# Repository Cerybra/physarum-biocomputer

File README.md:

<div align="center">
	<h1>Physarum Biocomputer</h1>
</div>

<hr/>

<hr/>

## Project Structure

#### Descriptions

The project structure is organized as follows:

- 📂 `adaptors`: contains all of the hardware files for the various adaptors that are compatible with the biocomputer carrier board.

- 📂 `data`: contains all of the experimentally collected data.

- 📂 `devices`: contains all of the hardware files for both the open-air and enclosure-type devices.

- 📂 `modules`: contains all of the hardware files for each of the biocomputer modules.

- 📂 `software`: contains all of the software used in performing experiments.

- 📂 `simulations`: contains all of the code used in performing equivalent circuit simulations.

- 📂 `plots`: contains all of the code used in producing the main figures.

#### Structure
📂 `repository` 

- 📂 `data`
	- 📂 `device-pulse-recordings` 
	- 📂 `device-regression-recordings` 
	- 📂 `device-sweep-recordings` 
	- 📂 `eis-recordings`
	- 📂 `noise-recordings`
	- 📂 `reservoir-computing-recordings`
- 📂 `modules`
    - 📂 `biocomputer-eval-motherboard`
    - 📂 `dac-eval-module`
    - 📂 `daq-eval-board`
    - 📂 `dual-rail-power-eval-module`
    - 📂 `selector-eval-module`
- 📂 `adaptors`
    - 📂 `1x1-adaptor`
    - 📂 `4x1-adaptor`
	- 📂 `8x1-adaptor`
    - 📂 `card-half`
    - 📂 `card-full`
    - 📂 `configurable-adaptor`
    - 📂 `standard-adaptor`
- 📂 `software`
    - 📂 `examples`
- 📂 `devices`
    - 📂 `enclosures`
    - 📂 `pluggable`
- 📂 `simulations`
- 📂 `plots`

## Reproducibility

To reproduce all of the main figures, either clone the repository or download the `data` directory. Then, run each of the scripts within the `plots/main` directory.

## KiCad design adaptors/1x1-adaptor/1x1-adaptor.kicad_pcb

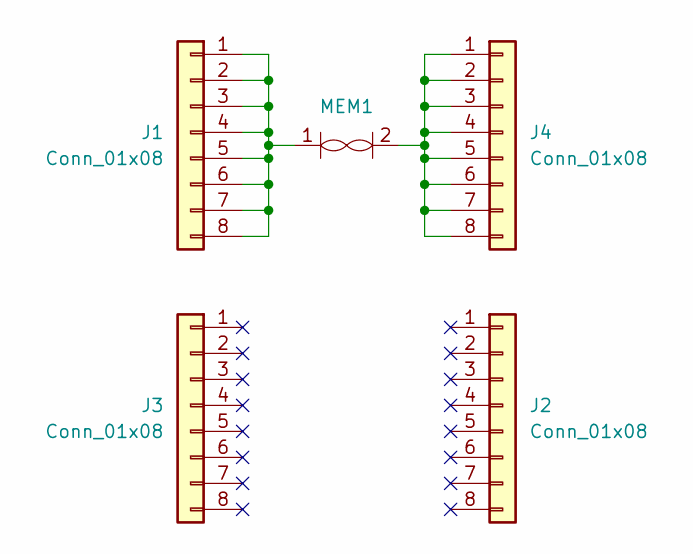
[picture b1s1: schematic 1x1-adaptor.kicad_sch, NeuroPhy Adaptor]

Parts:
J1, J2, J3, J4: Conn_01x08; PinHeader_1x08_P2.54mm_Vertical
MEM1: NeuroPhy_Memristor_5x5mm

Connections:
unnamed: J1.1, J1.2, J1.3, J1.4, J1.5, J1.6, J1.7, J1.8, MEM1.1
unnamed: J4.1, J4.2, J4.3, J4.4, J4.5, J4.6, J4.7, J4.8, MEM1.2

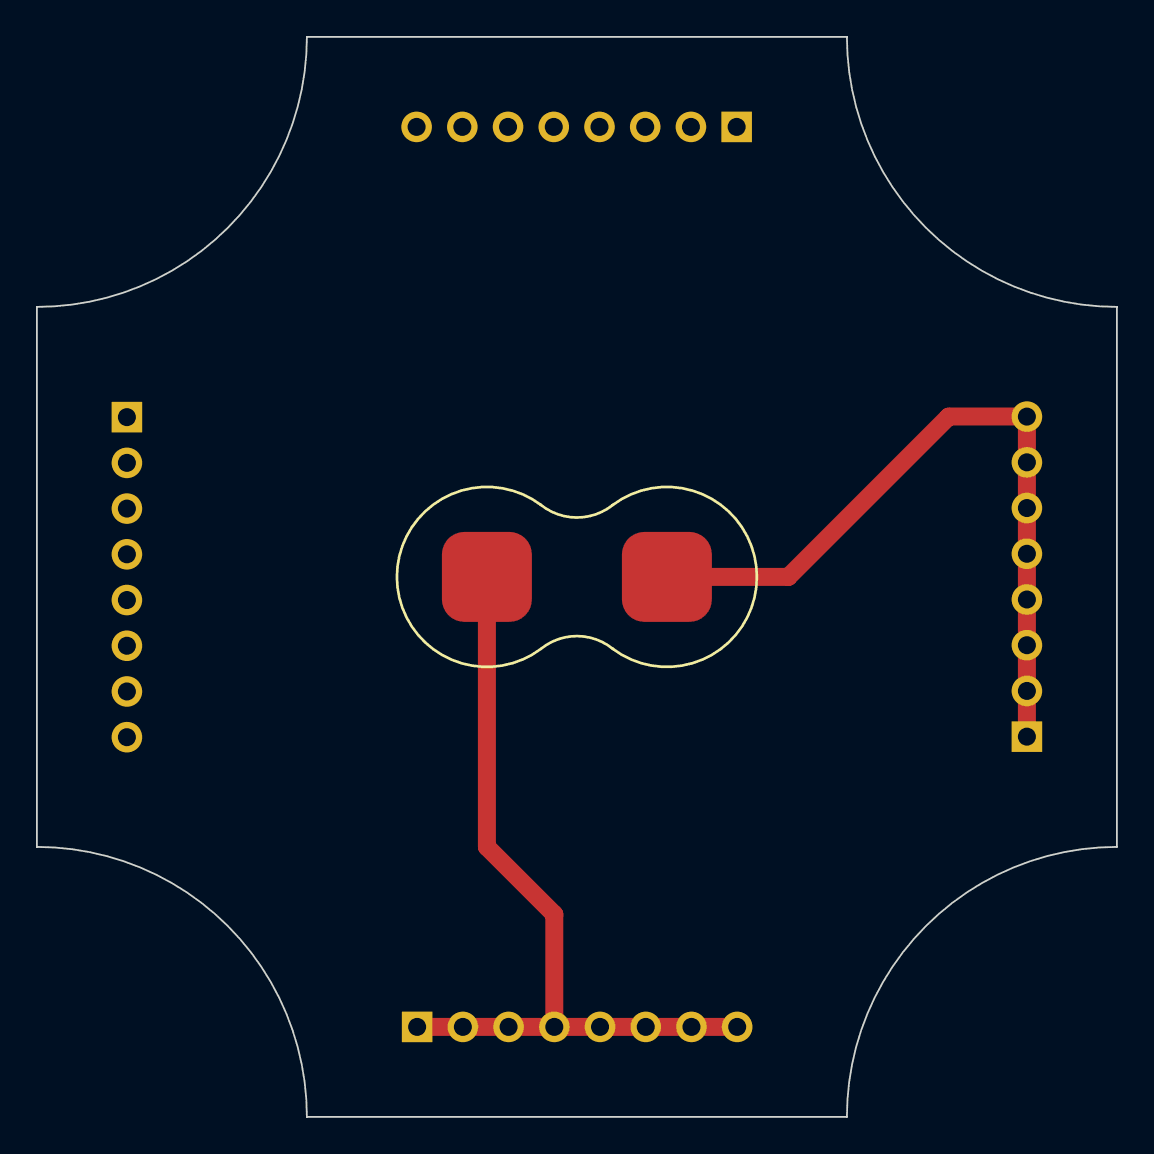
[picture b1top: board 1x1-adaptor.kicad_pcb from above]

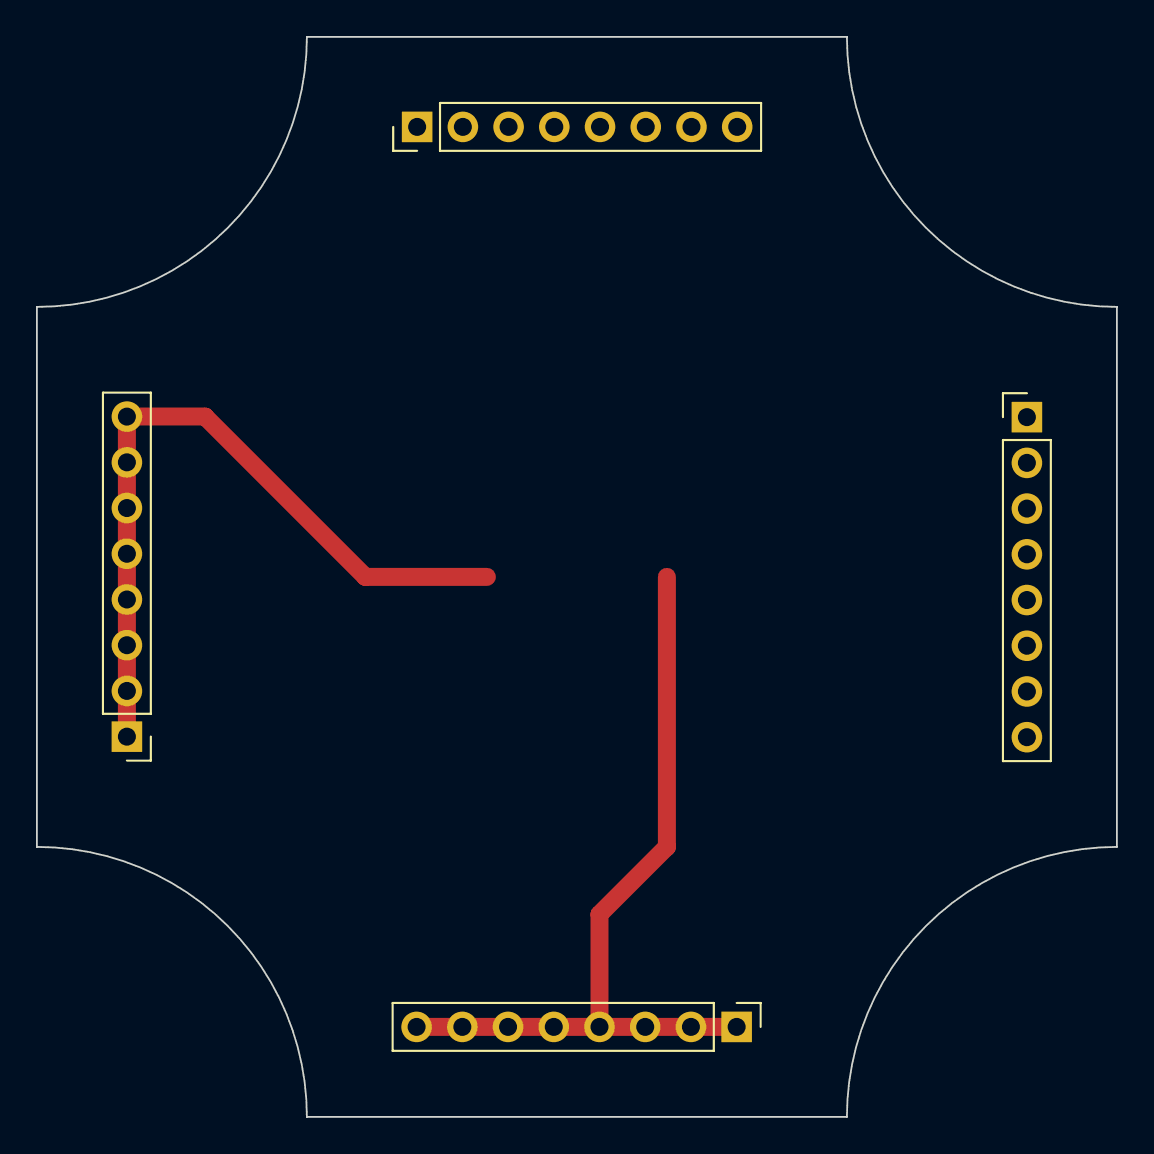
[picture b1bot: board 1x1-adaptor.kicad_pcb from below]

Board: 2 copper layers, 60.0 x 60.0 mm, 5 parts (4 on the bottom side), 2 nets.

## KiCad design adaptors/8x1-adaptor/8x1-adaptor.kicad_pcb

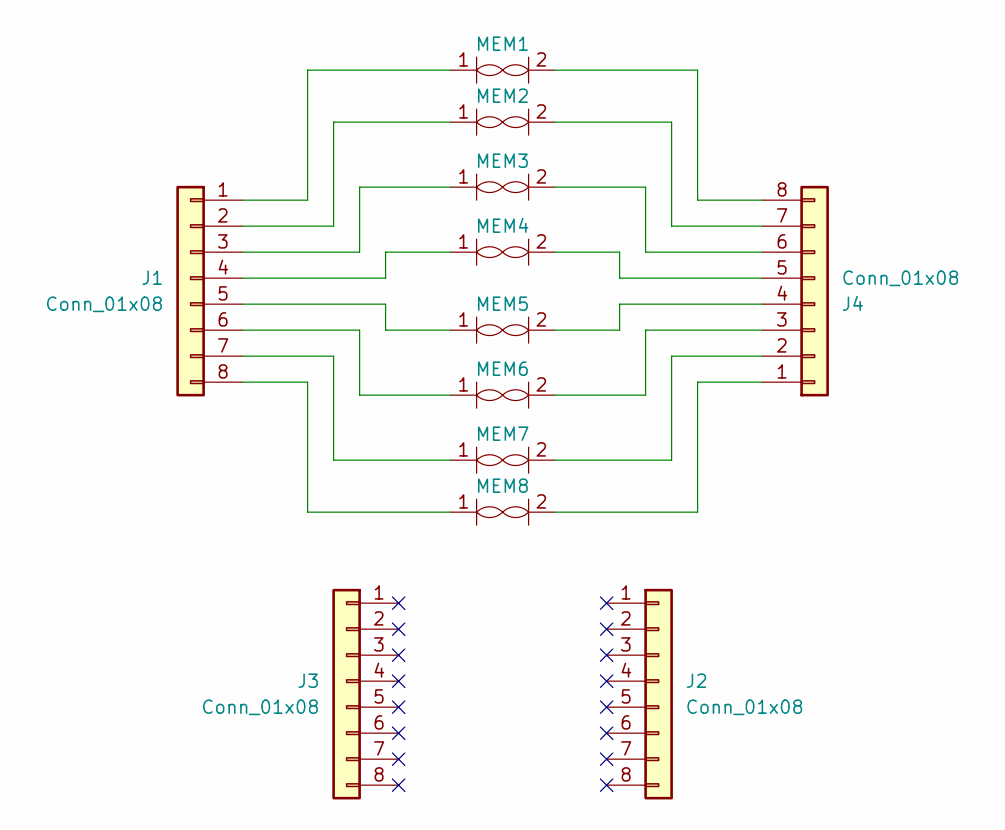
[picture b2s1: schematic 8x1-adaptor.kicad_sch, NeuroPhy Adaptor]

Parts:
J1, J2, J3, J4: Conn_01x08; PinHeader_1x08_P2.54mm_Vertical
MEM1, MEM2, MEM3, MEM4, MEM5, MEM6, MEM7, MEM8: NeuroPhy_Memristor_5x5mm

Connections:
unnamed: J1.1, MEM1.1
unnamed: J1.2, MEM2.1
unnamed: J1.3, MEM3.1
unnamed: J1.4, MEM4.1
unnamed: J1.5, MEM5.1
unnamed: J1.6, MEM6.1
unnamed: J1.7, MEM7.1
unnamed: J1.8, MEM8.1
unnamed: J4.1, MEM8.2
unnamed: J4.2, MEM7.2
unnamed: J4.3, MEM6.2
unnamed: J4.4, MEM5.2
unnamed: J4.5, MEM4.2
unnamed: J4.6, MEM3.2
unnamed: J4.7, MEM2.2
unnamed: J4.8, MEM1.2

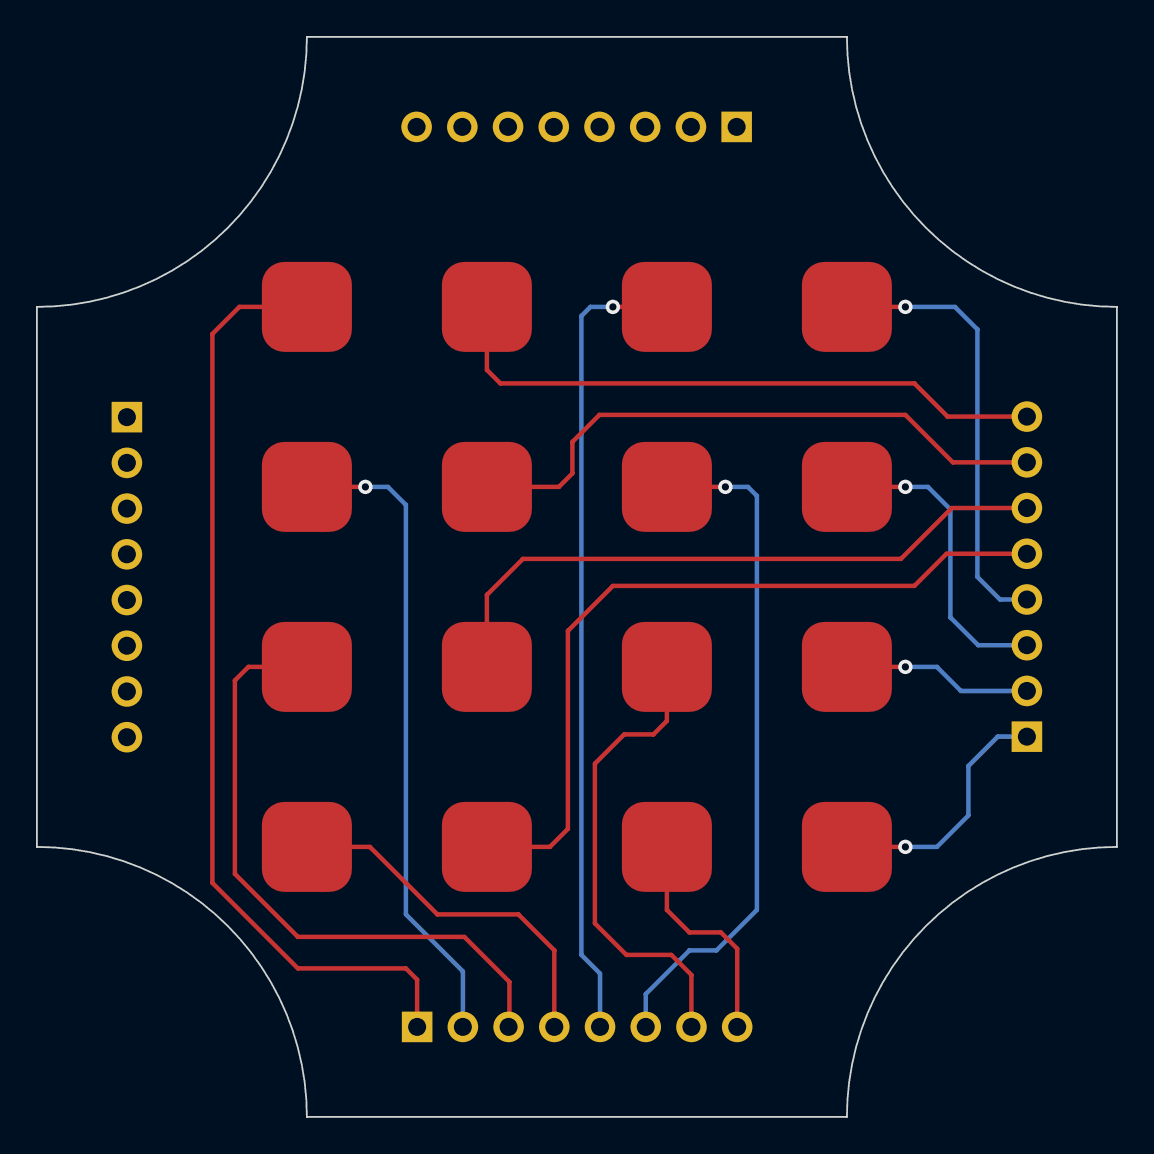
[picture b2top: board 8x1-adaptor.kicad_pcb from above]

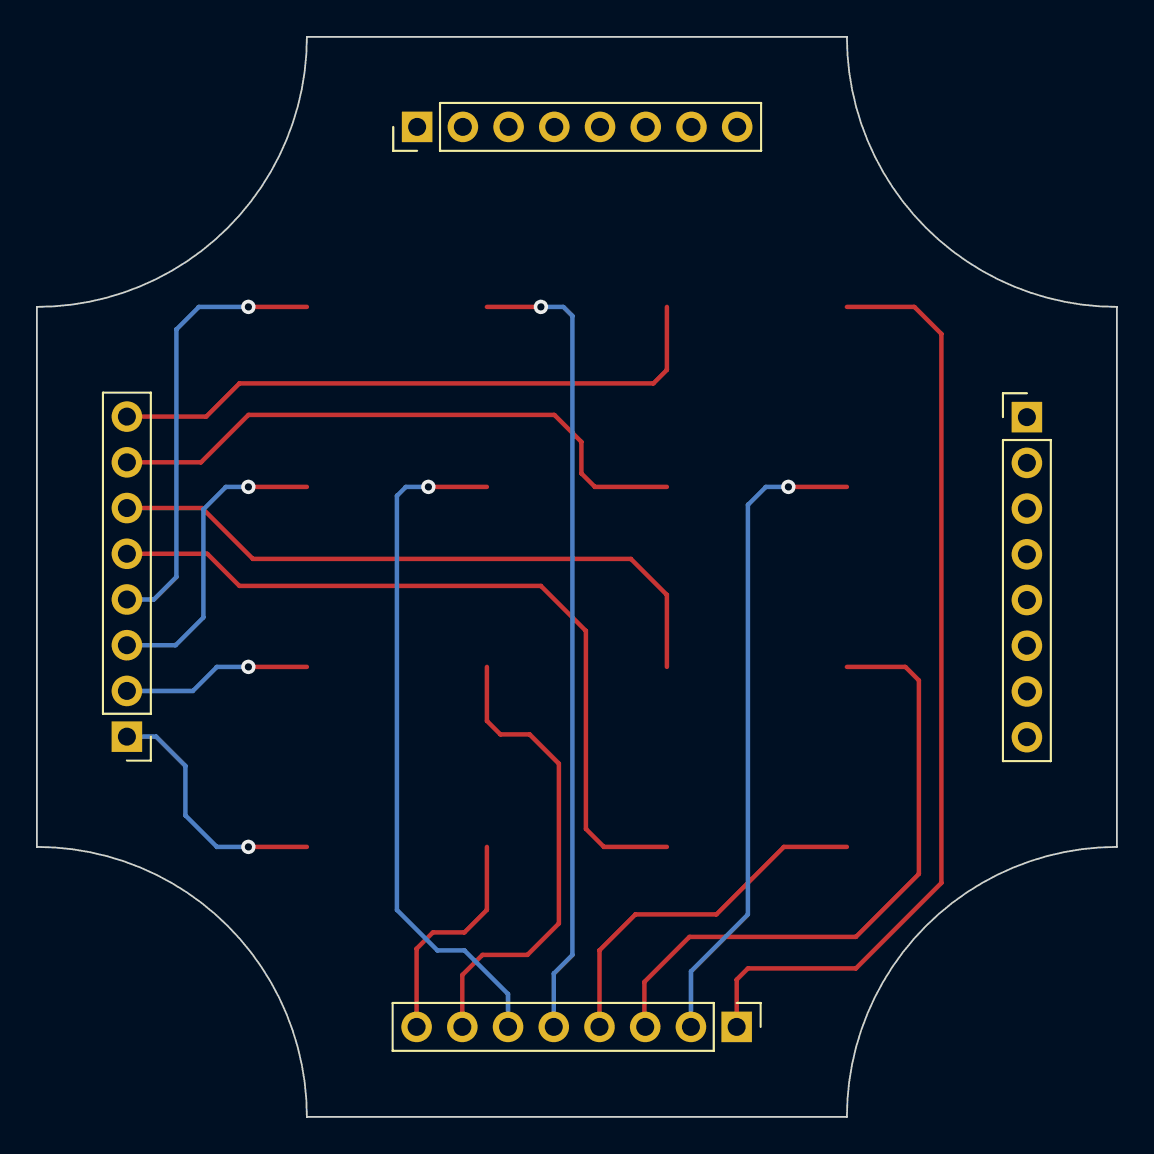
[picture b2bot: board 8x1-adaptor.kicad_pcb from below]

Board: 2 copper layers, 60.0 x 60.0 mm, 12 parts (4 on the bottom side), 16 nets.

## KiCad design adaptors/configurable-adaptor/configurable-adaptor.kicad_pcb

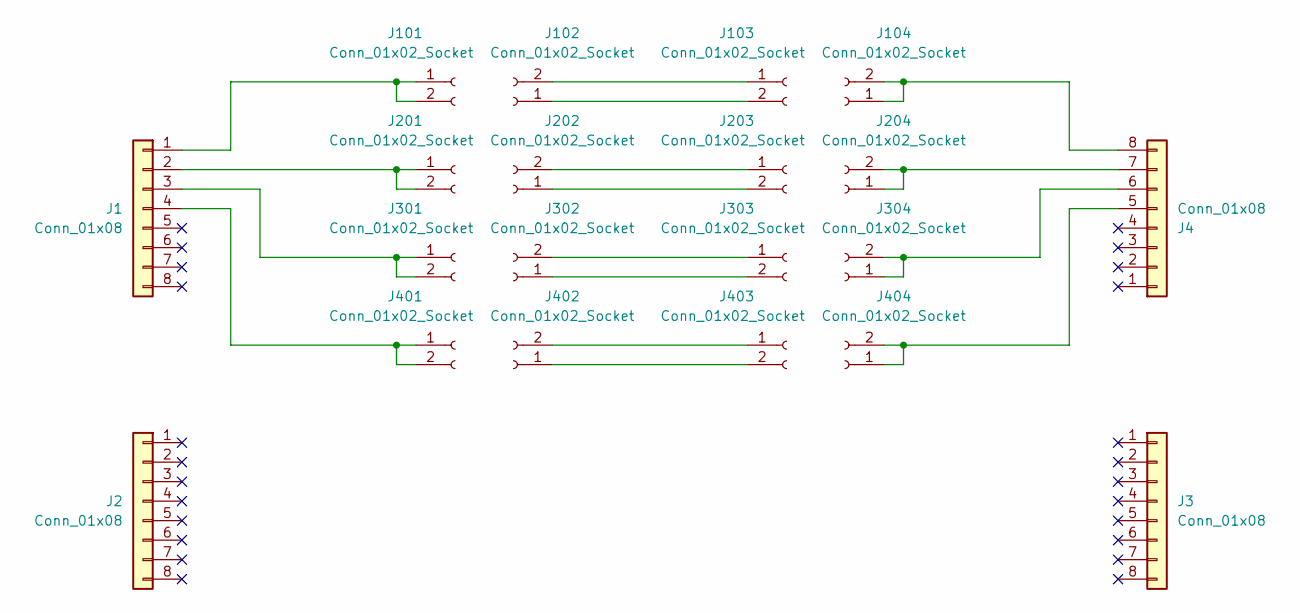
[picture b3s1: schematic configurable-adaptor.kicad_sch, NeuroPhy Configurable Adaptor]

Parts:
J1, J2, J3, J4: Conn_01x08; PinHeader_1x08_P2.54mm_Vertical
J101, J102, J103, J104, J201, J202, J203, J204, J301, J302, J303, J304, J401, J402, J403, J404: Conn_01x02_Socket; PinSocket_1x02_P2.54mm_Vertical

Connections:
unnamed: J1.1, J101.1, J101.2
unnamed: J1.2, J201.1, J201.2
unnamed: J1.3, J301.1, J301.2
unnamed: J1.4, J401.1, J401.2
unnamed: J4.5, J404.1, J404.2
unnamed: J102.1, J103.2
unnamed: J102.2, J103.1
unnamed: J4.8, J104.1, J104.2
unnamed: J202.1, J203.2
unnamed: J202.2, J203.1
unnamed: J4.7, J204.1, J204.2
unnamed: J302.1, J303.2
unnamed: J302.2, J303.1
unnamed: J4.6, J304.1, J304.2
unnamed: J402.1, J403.2
unnamed: J402.2, J403.1

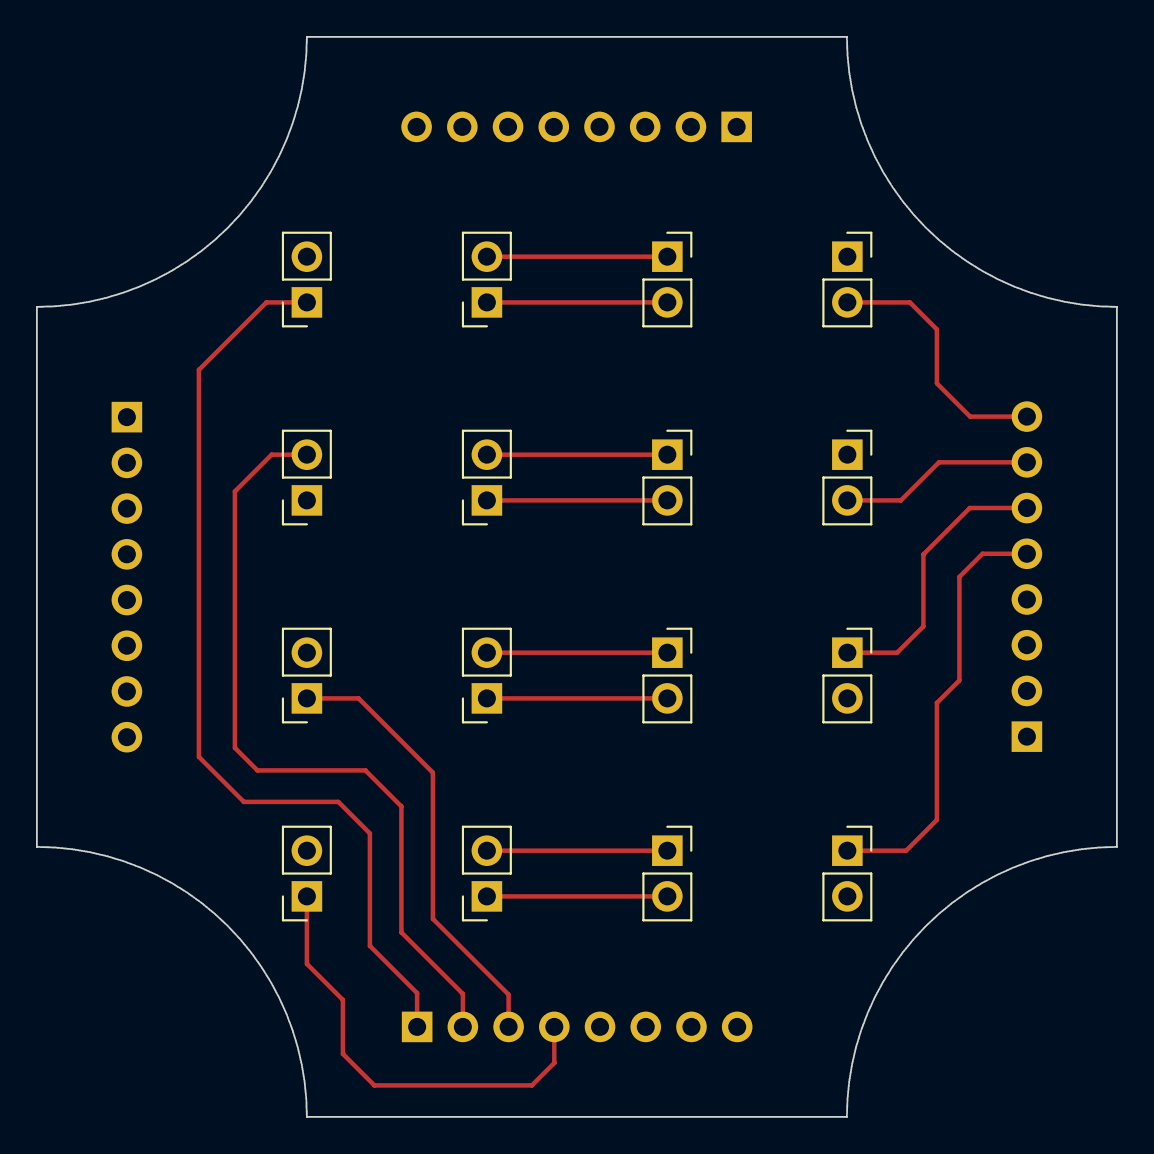
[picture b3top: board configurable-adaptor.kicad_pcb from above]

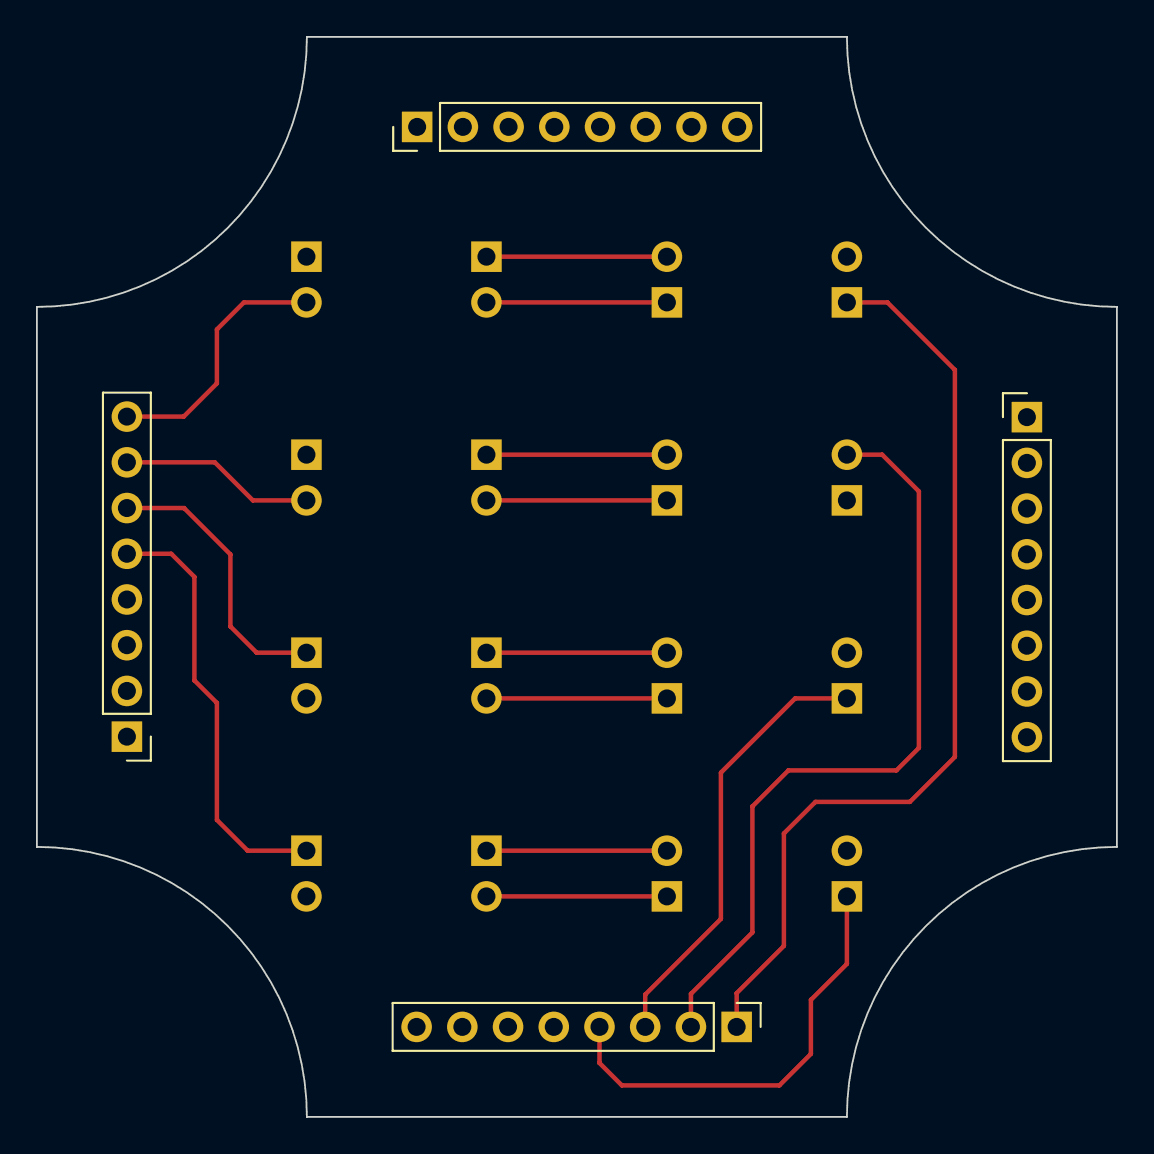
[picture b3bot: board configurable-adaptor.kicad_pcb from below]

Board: 2 copper layers, 60.0 x 60.0 mm, 20 parts (4 on the bottom side), 16 nets.

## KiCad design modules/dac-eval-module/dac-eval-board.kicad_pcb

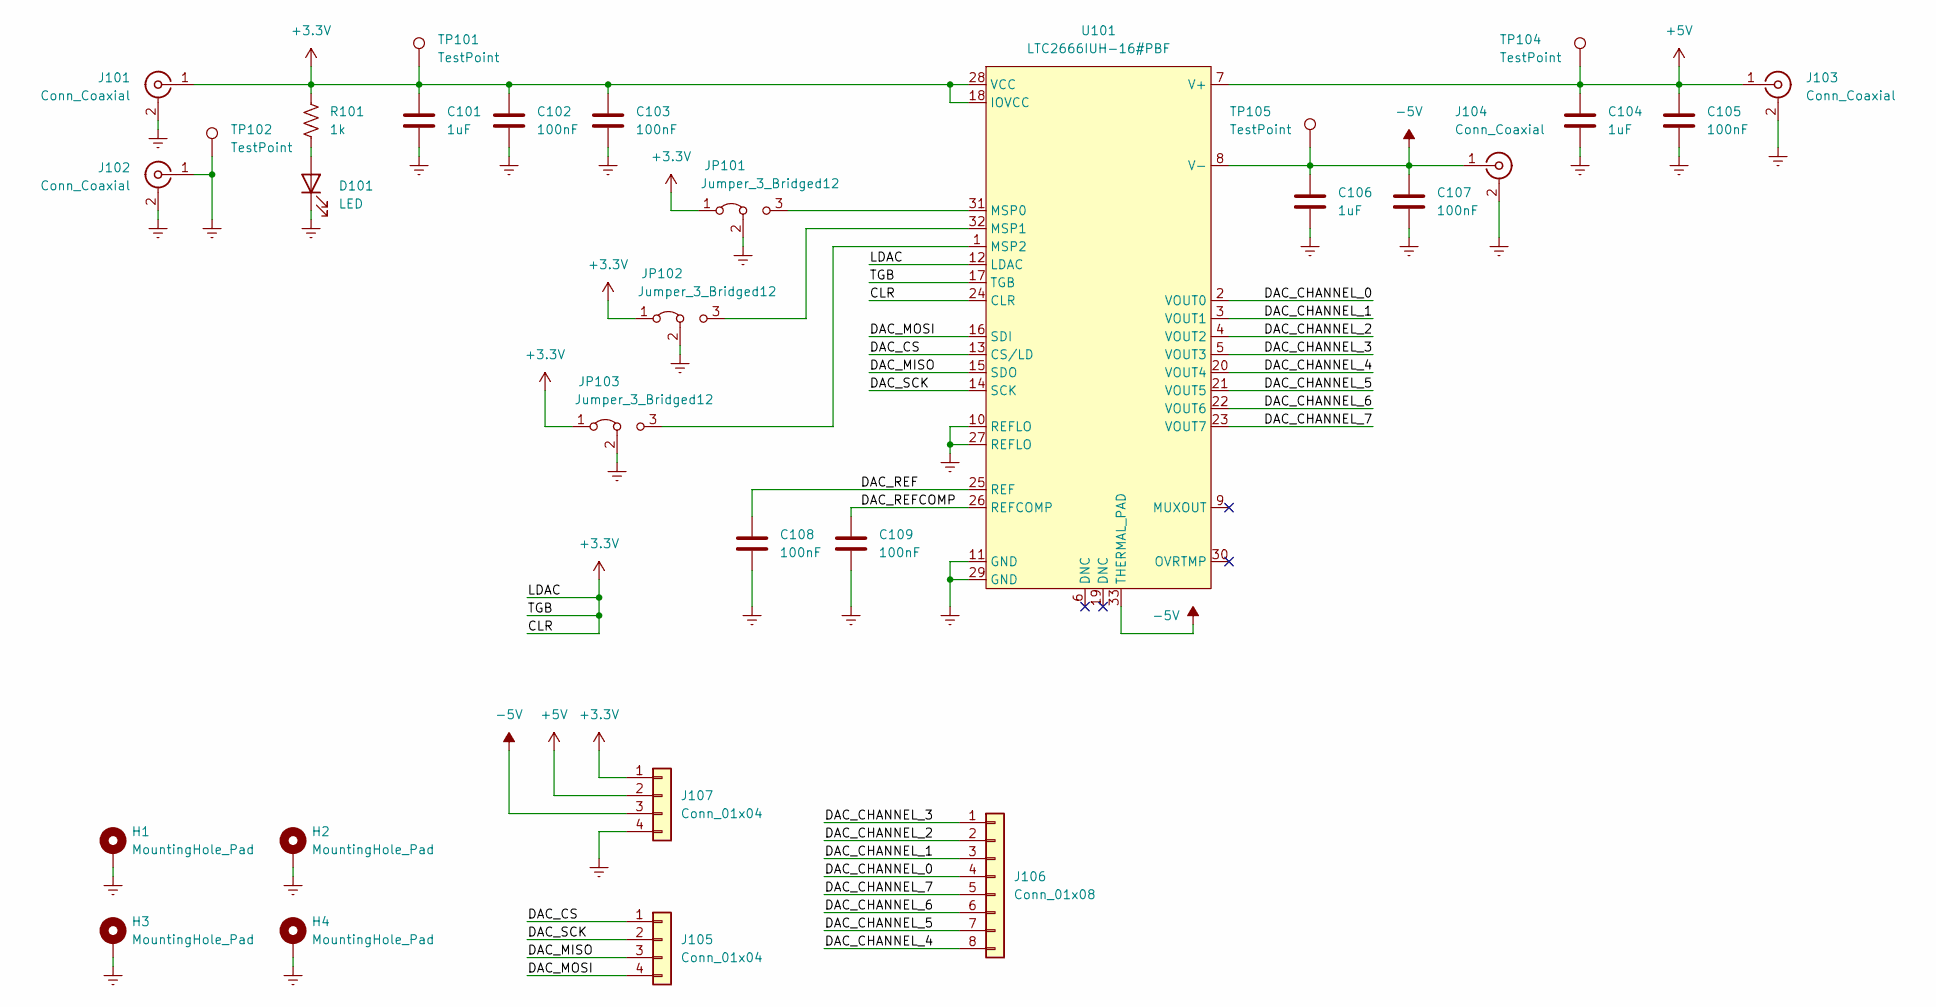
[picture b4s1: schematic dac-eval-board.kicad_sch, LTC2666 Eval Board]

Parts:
C101, C104, C106: 1uF; C_0402_1005Metric
C102, C103, C105, C107, C108, C109: 100nF; C_0402_1005Metric
D101: LED; LED_0603_1608Metric
H1, H2, H3, H4: MountingHole_Pad; MountingHole_2.7mm_Pad_Via
J101, J102, J103, J104: Conn_Coaxial; CONN_RF2-04A-T-00-50-G_ADM
J105, J107: Conn_01x04; PinHeader_1x04_P2.54mm_Vertical
J106: Conn_01x08; PinHeader_1x08_P2.54mm_Vertical
JP101, JP102, JP103: Jumper_3_Bridged12; PinHeader_1x03_P2.54mm_Vertical
R101: 1k; R_0603_1608Metric
TP101, TP104, TP105: TestPoint; KEYSTONE_5000
TP102: TestPoint; KEYSTONE_5001
U101: LTC2666IUH-16#PBF; QFN-32-1EP_5x5mm_P0.5mm_EP3.45x3.45mm

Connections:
+3.3V: C101.1, C102.1, C103.1, J101.1 (In), J107.1, JP101.1 (A), JP102.1 (A), JP103.1 (A), R101.1, TP101.1, U101.12 (LDAC), U101.17 (TGB), U101.18 (IOVCC), U101.24 (CLR), U101.28 (VCC)
+5V: C104.1, C105.1, J103.1 (In), J107.2, TP104.1, U101.7 (V+)
-5V: C106.1, C107.1, J104.1 (In), J107.3, TP105.1, U101.8 (V-), U101.33 (THERMAL_PAD)
/DAC_CHANNEL_0: J106.4, U101.2 (VOUT0)
/DAC_CHANNEL_1: J106.3, U101.3 (VOUT1)
/DAC_CHANNEL_2: J106.2, U101.4 (VOUT2)
/DAC_CHANNEL_3: J106.1, U101.5 (VOUT3)
/DAC_CHANNEL_4: J106.8, U101.20 (VOUT4)
/DAC_CHANNEL_5: J106.7, U101.21 (VOUT5)
/DAC_CHANNEL_6: J106.6, U101.22 (VOUT6)
/DAC_CHANNEL_7: J106.5, U101.23 (VOUT7)
/DAC_CS: J105.1, U101.13 (CS/LD)
/DAC_MISO: J105.3, U101.15 (SDO)
/DAC_MOSI: J105.4, U101.16 (SDI)
/DAC_REF: C108.1, U101.25 (REF)
/DAC_REFCOMP: C109.1, U101.26 (REFCOMP)
/DAC_SCK: J105.2, U101.14 (SCK)
Earth: C101.2, C102.2, C103.2, C104.2, C105.2, C106.2, C107.2, C108.2, C109.2, D101.1 (K), H1.1, H2.1, H3.1, H4.1, J101.2 (Ext), J102.1 (In), J102.2 (Ext), J103.2 (Ext), J104.2 (Ext), J107.4, JP101.2 (C), JP102.2 (C), JP103.2 (C), TP102.1, U101.10 (REFLO), U101.11 (GND), U101.27 (REFLO), U101.29 (GND)
unnamed: D101.2 (A), R101.2
unnamed: JP101.3 (B), U101.31 (MSP0)
unnamed: JP102.3 (B), U101.32 (MSP1)
unnamed: JP103.3 (B), U101.1 (MSP2)

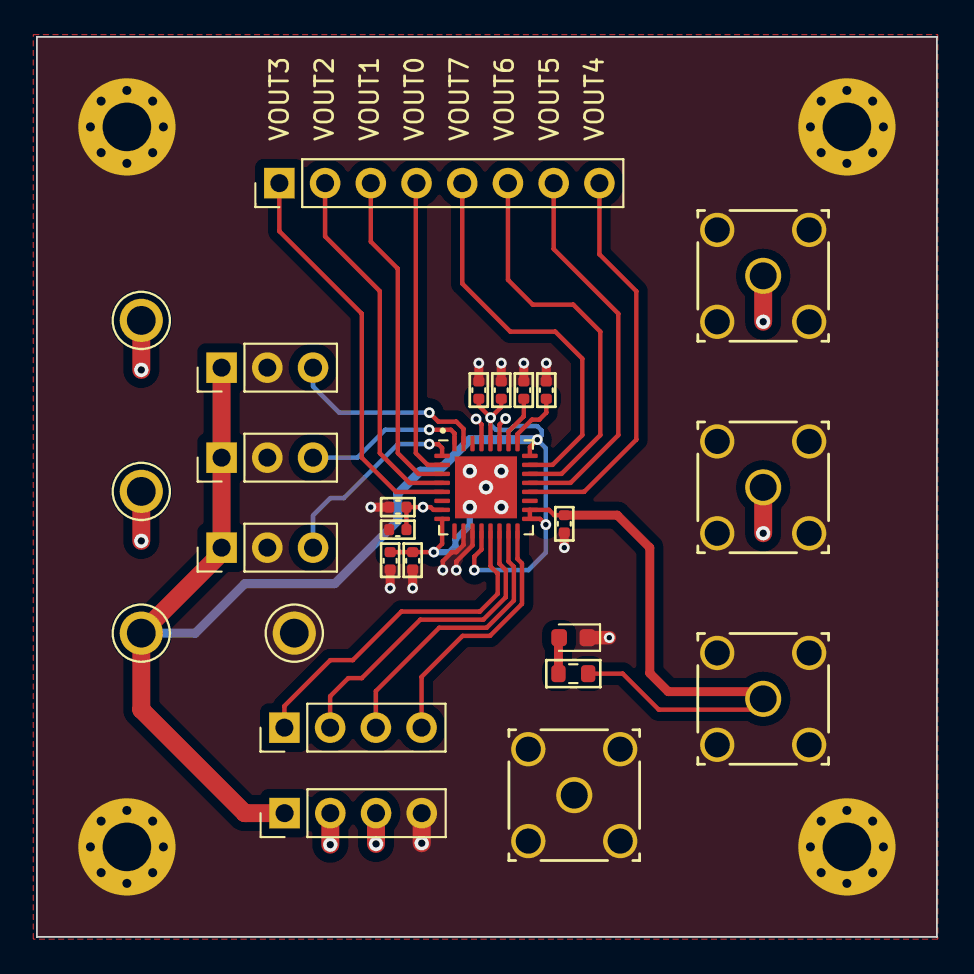
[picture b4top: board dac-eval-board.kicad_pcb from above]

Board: 6 copper layers, 50.0 x 50.0 mm, 30 parts (0 on the bottom side), 22 nets.

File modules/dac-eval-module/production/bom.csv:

Comment,Designator,Footprint,LCSC Part #
1uF Unpolarized capacitor,"C101,C104,C106",C_0402_1005Metric,
100nF Unpolarized capacitor,"C102,C103,C105,C107,C108,C109",C_0402_1005Metric,
LED Light emitting diode,D101,LED_0603_1608Metric,
"Conn_Coaxial coaxial connector (BNC, SMA, SMB, SMC, Cinch/RCA, LEMO, ...)","J101,J102,J103,J104",CONN_RF2-04A-T-00-50-G_ADM,
"1k Resistor, US symbol",R101,R_0603_1608Metric,
TestPoint test point,"TP101,TP104,TP105",KEYSTONE_5000,
TestPoint test point,TP102,KEYSTONE_5001,
LTC2666IUH-16#PBF Octal 16-Bit/12-Bit ±10V VOUT SoftSpan DACs with 10ppm/°C Max Reference,U101,QFN-32-1EP_5x5mm_P0.5mm_EP3.45x3.45mm,

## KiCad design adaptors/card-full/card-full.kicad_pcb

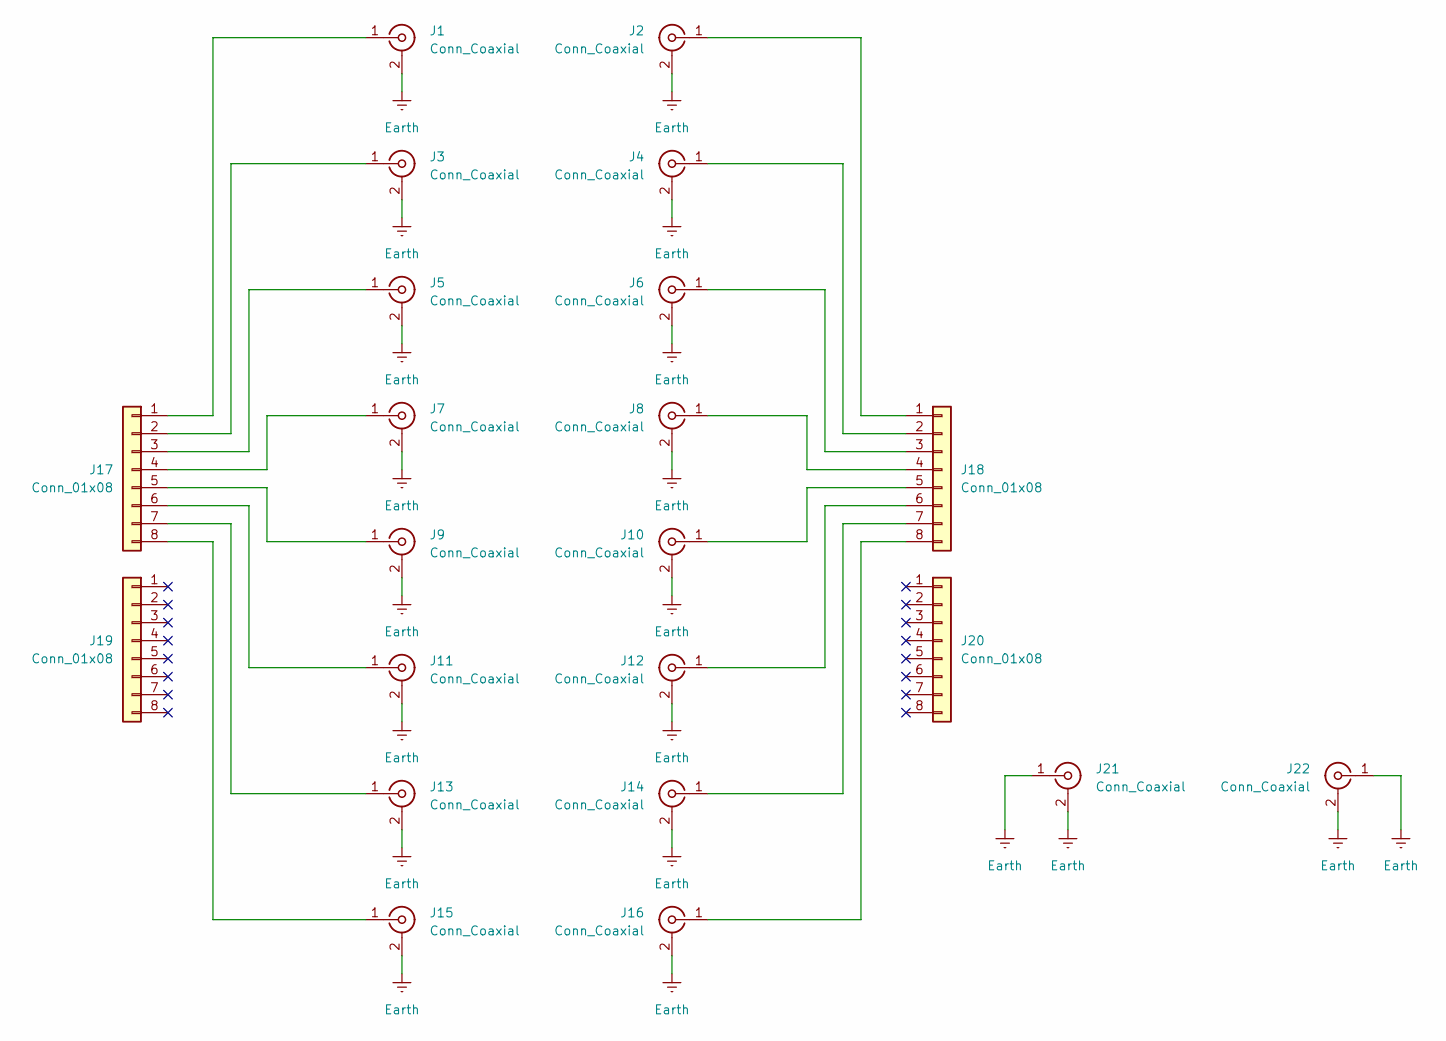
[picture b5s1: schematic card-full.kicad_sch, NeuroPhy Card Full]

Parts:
J1, J2, J3, J4, J5, J6, J7, J8, J9, J10, J11, J12, J13, J14, J15, J16: Conn_Coaxial; 1333801201
J17, J18, J19, J20: Conn_01x08; PinHeader_1x08_P2.54mm_Vertical
J21, J22: Conn_Coaxial; SMA_Amphenol_132134-11_Vertical

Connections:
Earth: J1.2 (Ext), J2.2 (Ext), J3.2 (Ext), J4.2 (Ext), J5.2 (Ext), J6.2 (Ext), J7.2 (Ext), J8.2 (Ext), J9.2 (Ext), J10.2 (Ext), J11.2 (Ext), J12.2 (Ext), J13.2 (Ext), J14.2 (Ext), J15.2 (Ext), J16.2 (Ext), J21.1 (In), J21.2 (Ext), J22.1 (In), J22.2 (Ext)
unnamed: J1.1 (In), J17.1
unnamed: J10.1 (In), J18.5
unnamed: J11.1 (In), J17.6
unnamed: J12.1 (In), J18.6
unnamed: J13.1 (In), J17.7
unnamed: J14.1 (In), J18.7
unnamed: J15.1 (In), J17.8
unnamed: J16.1 (In), J18.8
unnamed: J3.1 (In), J17.2
unnamed: J5.1 (In), J17.3
unnamed: J7.1 (In), J17.4
unnamed: J9.1 (In), J17.5
unnamed: J2.1 (In), J18.1
unnamed: J4.1 (In), J18.2
unnamed: J6.1 (In), J18.3
unnamed: J8.1 (In), J18.4

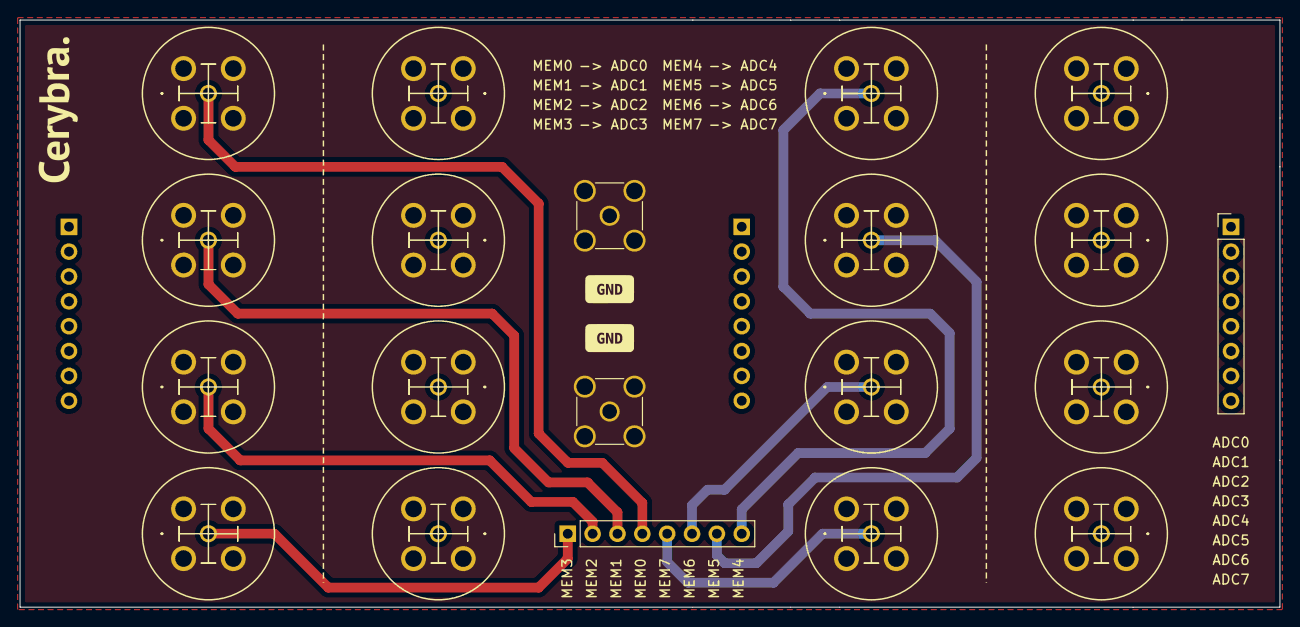
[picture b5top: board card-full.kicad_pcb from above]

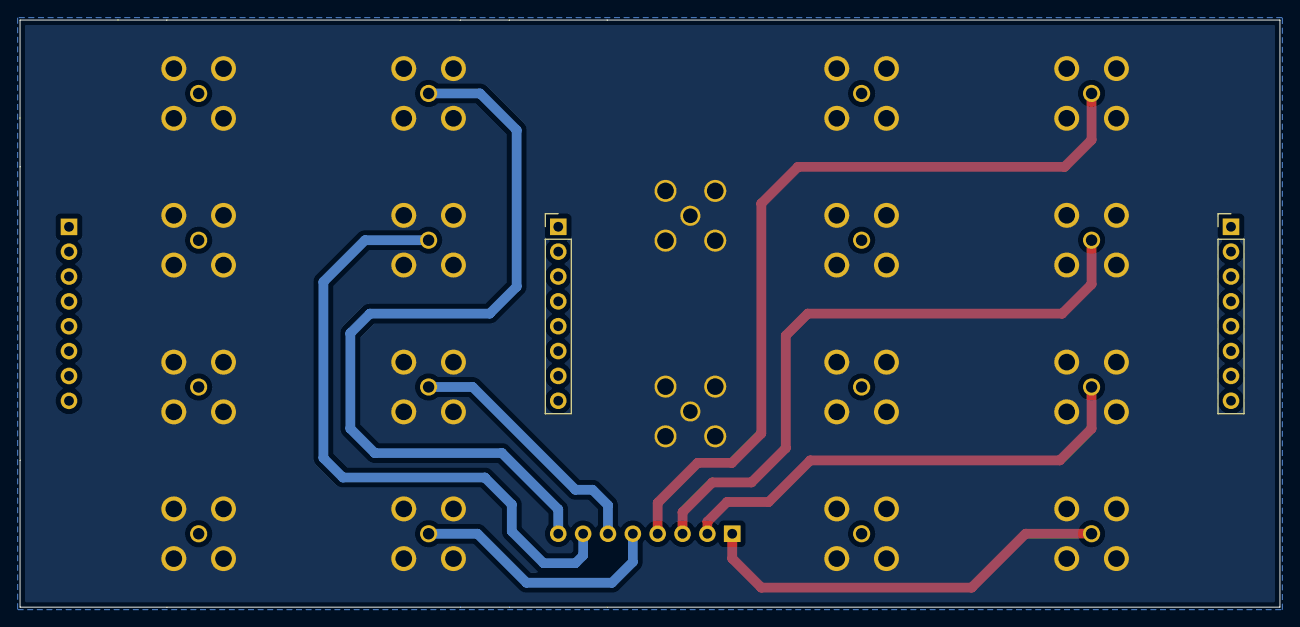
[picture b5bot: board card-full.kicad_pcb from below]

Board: 6 copper layers, 128.8 x 60.0 mm, 22 parts (2 on the bottom side), 17 nets.

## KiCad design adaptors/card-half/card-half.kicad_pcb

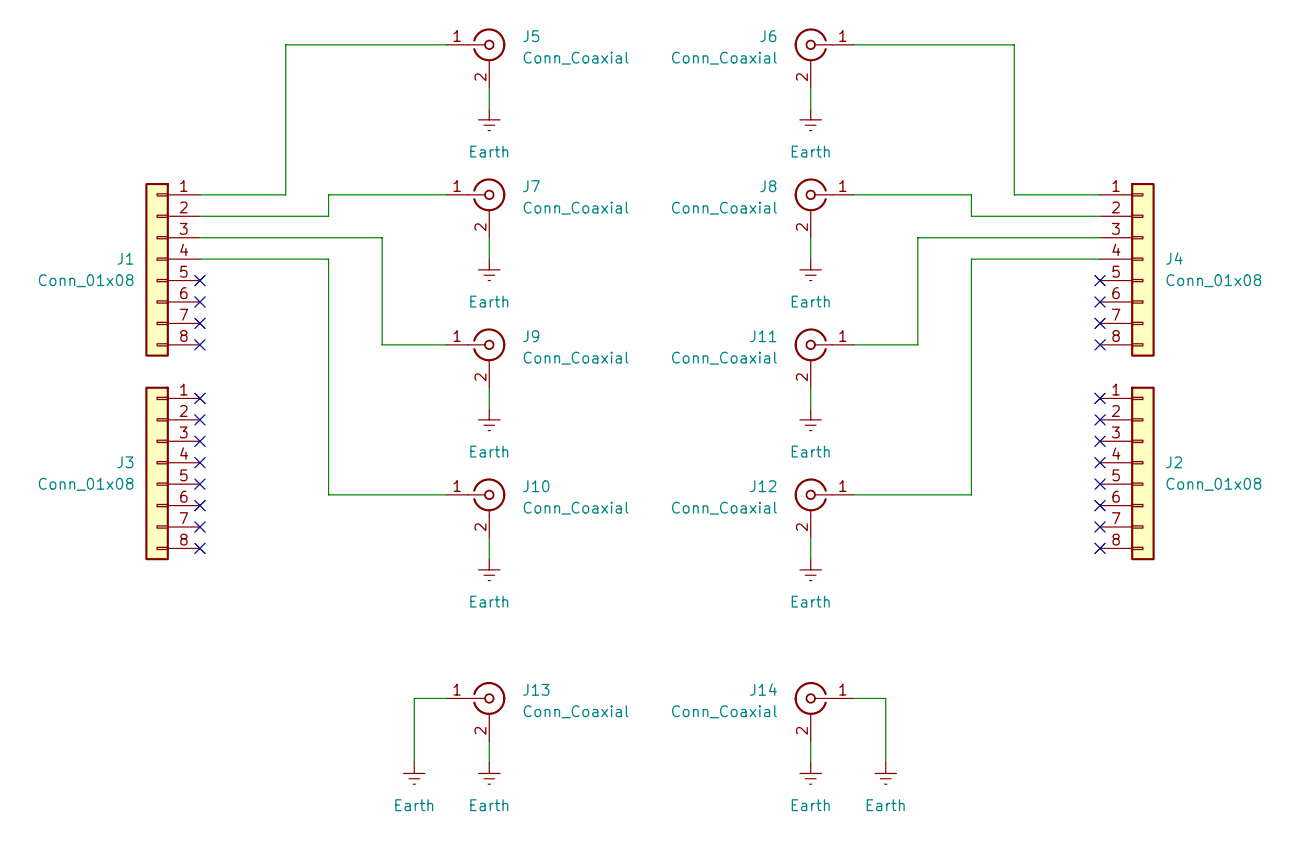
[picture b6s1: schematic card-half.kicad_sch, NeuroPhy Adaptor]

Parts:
J1, J2, J3, J4: Conn_01x08; PinHeader_1x08_P2.54mm_Vertical
J5, J6, J7, J8, J9, J10, J11, J12: Conn_Coaxial; 1333801201
J13, J14: Conn_Coaxial; SMA_Amphenol_132134-11_Vertical

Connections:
Earth: J5.2 (Ext), J6.2 (Ext), J7.2 (Ext), J8.2 (Ext), J9.2 (Ext), J10.2 (Ext), J11.2 (Ext), J12.2 (Ext), J13.1 (In), J13.2 (Ext), J14.1 (In), J14.2 (Ext)
unnamed: J1.1, J5.1 (In)
unnamed: J1.2, J7.1 (In)
unnamed: J1.3, J9.1 (In)
unnamed: J1.4, J10.1 (In)
unnamed: J4.1, J6.1 (In)
unnamed: J4.2, J8.1 (In)
unnamed: J4.3, J11.1 (In)
unnamed: J4.4, J12.1 (In)
